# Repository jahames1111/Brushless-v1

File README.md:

# Brushless-v1
This will hopefully be my first real working drone. Previously, I have built things using brushed 8520 motors, but I could never get the drone to be light enough for those to work. This time, I will have a bigger budget and will be able to use brushless motors. 

3D: In github, also
https://cad.onshape.com/documents/dc8006e672f3f91329fdcc5b 
 
https://cad.onshape.com/documents/e8c6850fa68e1cd546790438 
 
https://cad.onshape.com/documents/d17096ea64e2407efe53b08a 

# BOM (so far)
|Part                                                            |Type      |Quantity|Unit price (USD)|Line total (USD)|Link                                                                                       |Vendor               |Funding    |Notes                                                  |
|----------------------------------------------------------------|----------|--------|----------------|----------------|-------------------------------------------------------------------------------------------|---------------------|-----------|-------------------------------------------------------|
|1203 6500KV 2-4S Brushless Motors (4PCS)                        |Part      |1       |39.99           |39.99           |https://www.amazon.com/SPARKHOBBY-Brushless-FPVRacer-Freestyle-Cinewhoop/dp/B0FF349Z37     |Amazon               |Grant      |4-pack 1.5mm shaft motors                              |
|CORVON 30A 4-in-1 Brushless ESC (6V-18V, 20x20mm)               |Part      |1       |26.99           |26.99           |https://www.amazon.com/CORVON-Brushless-Supports-Oneshot-Lightweight/dp/B0GTTVMRMG         |Amazon               |Grant      |2S-4S PWM/DShot 4-in-1 ESC                             |
|OVONIC 7.6V 100C 450mAh 2S LiPo Battery with XT30 (2-Pack)      |Part      |1       |20.37           |20.37           |https://www.amazon.com/OVONIC-Battery-Package-Including-Batteries/dp/B0D3F5SQ5T            |Amazon               |Grant      |Standard non-Prime price ($13.44 with Prime)           |
|JLC3DP PA12-HP Nylon 3D-Printed Drone Frame (frame (2).step)    |Part      |2       |8.28            |16.56           |https://jlc3dp.com/                                                                        |JLC3DP               |Grant      |MJF PA12-HP Nylon, Black, 2pcs                         |
|AOICRIE GY-521 MPU-6050 6-DOF Gyro/Accelerometer Module (3-Pack)|Part      |1       |14.99           |14.99           |https://www.amazon.com/AOICRIE-GY-521-Accelerometer-Gyroscope-Pre-Soldered/dp/B0D2TJVMNY   |Amazon               |Grant      |Pre-soldered headers, I2C IMU                          |
|Gemfan 3016 3-Blade 3-Inch Propellers 1.5mm Hole (16pcs)        |Part      |1       |12.98           |12.98           |https://www.amazon.com/Propeller-1108-1308-Brushless-Toothpick-Quadcopters/dp/B0DZPBVDD8   |Amazon               |Grant      |8 CW + 8 CCW props                                     |
|2.4GHz ELRS T-Receiver Antenna 100mm IPEX1 (3PCS)               |Part      |1       |9.99            |9.99            |https://www.amazon.com/2-4GHz-Antenna-90MM-ELRS-Compatible/dp/B0G7F842V8                   |Amazon               |Grant      |For ESP-NOW LR external antenna                        |
|ZHOFONET XT30 Male/Female Pigtail 16AWG Silicone Wire (5 Pairs) |Part      |1       |8.99            |8.99            |https://www.amazon.com/ZHOFONET-Pigtail-Female-Connector-Silicone/dp/B09F3CLKBG            |Amazon               |Grant      |Main battery connector lead                            |
|Mini MP1584EN 5V 3A DC-DC Buck Converter Module (6-Pack)        |Part      |1       |7.98            |7.98            |https://www.amazon.com/Converter-Voltage-Regulator-MP1584EN-Adjustable/dp/B0GHRPDKHW       |Amazon               |Grant      |Steps 2S battery down to 5.0V                          |
|HiLetgo BMP280-3.3 Atmospheric Pressure Barometer Sensor (5pcs) |Part      |1       |7.39            |7.39            |https://www.amazon.com/HiLetgo-Precision-BMP280-3-3-Atmospheric-Pressure/dp/B07VNDZ6N4     |Amazon               |Grant      |3.3V I2C barometer                                     |
|JLCPCB Custom Carrier PCB (brushless_Y16, 5pcs)                 |Part      |1       |4.00            |4.00            |https://jlcpcb.com/                                                                        |JLCPCB               |Grant      |Green 1.6mm OSP carrier PCB (5-pack)                   |
|JLCPCB & JLC3DP Shipping                                        |Shipping  |1       |11.70           |11.70           |https://jlcpcb.com/                                                                        |JLCPCB / JLC3DP      |Grant      |Combined shipping for carrier PCB and 3D-printed frames|
|Amazon Shipping (1203 Motors)                                   |Shipping  |1       |1.50            |1.50            |https://www.amazon.com/SPARKHOBBY-Brushless-FPVRacer-Freestyle-Cinewhoop/dp/B0FF349Z37     |Amazon               |Grant      |Shipping fee for motor set                             |
|SH 8p connector kit                                             |Part      |1       |19.99           |0.00            |https://www.amazon.com/Pre-Crimped-Connectors-Compatible-controller-SpeedyBee/dp/B0D2MQ85LK|Amazon               |Already own|Already own ($19.99 value for reproducibility)         |
|Seeed Studio XIAO ESP32S3 Sense Microcontroller                 |Part      |1       |13.99           |0.00            |https://www.amazon.com/Seeed-Studio-XIAO-ESP32S3-Microcontroller/dp/B0C69FFVHH             |Seeed Studio / Amazon|Already own|Already own ($13.99 value for reproducibility)         |
|GY-NEO6MV2 NEO-6M GPS Module with Ceramic Antenna               |Part      |1       |8.99            |0.00            |https://www.amazon.com/GY-NEO6MV2-NEO-6M-Module-Ceramic-Antenna/dp/B01D1D0F5M              |Amazon               |Already own|Already own ($8.99 value for reproducibility)          |
|Tax                                                             |Tax or fee|1       |8.56            |8.56            |                                                                                           |                     |Grant      |VA 5.03% Tax on $170.23 parts subtotal                 |
|Total                                                           |          |        |                |191.99          |                                                                                           |                     |           |                                                       |

# Wiring/Connections on PCB

| Net Name | Function / Signal | All Connected Pins |
| :--- | :--- | :--- |
| `2s` | Battery Voltage (`VBAT`) | `J5` Pin 1, `J7` Pin 7, `J8` Pin 2 |
| `5` | Regulated `+5V` Rail | `J1` Pin 1, `J6` Pin 1 |
| `3` | Regulated `+3.3V` Rail | `J1` Pin 3, `J3` Pin 1, `J4` Pin 1, `J9` Pin 1 |
| `g` | Common Ground (`GND`) | `J1` Pin 2, `J3` Pin 2, `J4` Pin 2, `J5` Pin 4, `J6` Pin 4, `J7` Pin 8, `J8` Pin 3, `J9` Pin 4 |
| `1` | ESC Motor 1 (`D0`) | `J2` Pin 1, `J7` Pin 6 |
| `2` | ESC Motor 2 (`D1`) | `J2` Pin 2, `J7` Pin 5 |
| `3` | ESC Motor 3 (`D2`) | `J2` Pin 3, `J7` Pin 4 |
| `4` | ESC Motor 4 (`D3`) | `J2` Pin 4, `J7` Pin 3 |
| `sda` | Shared I2C Data | `J2` Pin 5, `J3` Pin 4, `J4` Pin 4 |
| `scl` | Shared I2C Clock | `J2` Pin 6, `J3` Pin 3, `J4` Pin 3 |
| `rx` | UART (`D6` ➔ GPS `RX`) | `J2` Pin 7, `J9` Pin 2 |
| `tx` | UART (`D7` ➔ GPS `TX`) | `J1` Pin 7, `J9` Pin 3 |
| `vadc` | Battery Voltage Sense | `J1` Pin 6, `J8` Pin 1 |
| *No-Connect* | Unused Pins | `J1` Pin 4, `J1` Pin 5, `J5` Pin 2, `J5` Pin 3, `J6` Pin 2, `J6` Pin 3, `J7` Pin 1, `J7` Pin 2 |

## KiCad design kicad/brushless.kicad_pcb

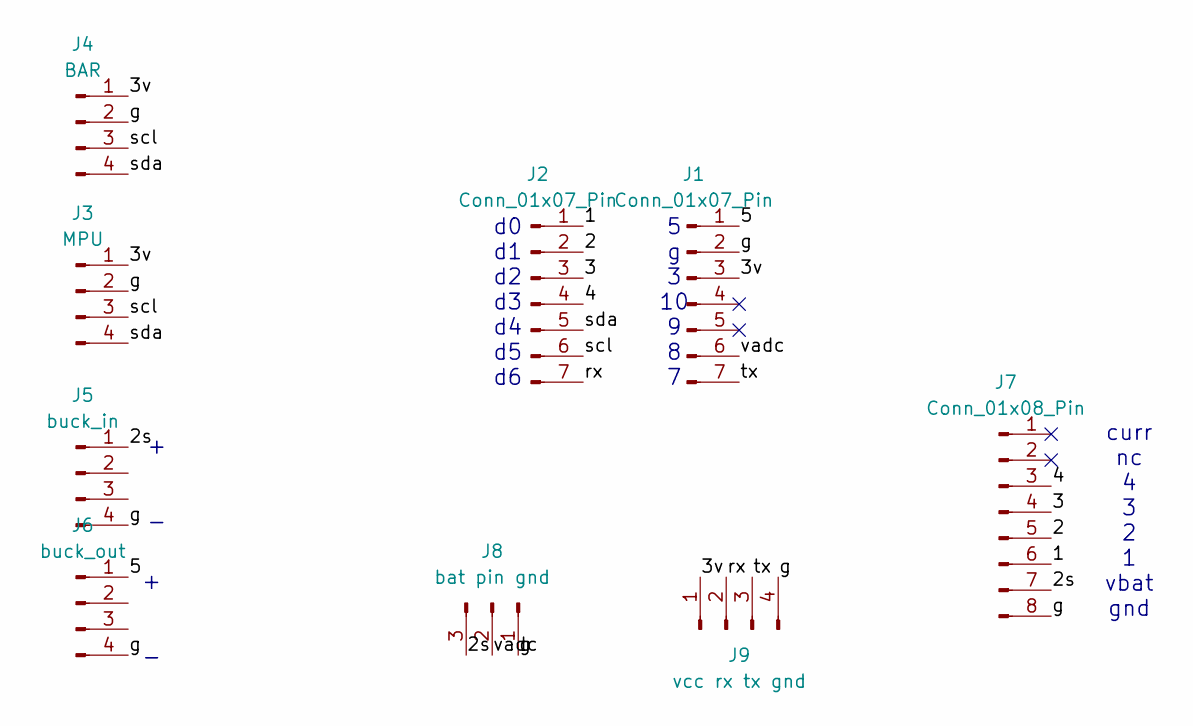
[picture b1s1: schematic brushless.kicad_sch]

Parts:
J1, J2: Conn_01x07_Pin; PinHeader_1x07_P2.54mm_Vertical
J3: MPU; PinHeader_1x04_P2.54mm_Vertical
J4: BAR; PinHeader_1x04_P2.54mm_Vertical
J5: buck_in; PinHeader_1x04_P2.54mm_Vertical
J6: buck_out; PinHeader_1x04_P2.54mm_Vertical
J7: Conn_01x08_Pin; PinHeader_1x08_P2.54mm_Vertical
J8: bat pin gnd; PinHeader_1x03_P2.54mm_Vertical
J9: vcc rx tx gnd; PinHeader_1x04_P2.54mm_Vertical

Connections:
/1: J2.1, J7.6
/2: J2.2, J7.5
/2s: J5.1, J7.7, J8.3
/3: J2.3, J7.4
/3v: J1.3, J3.1, J4.1, J9.1
/4: J2.4, J7.3
/5: J1.1, J6.1
/g: J1.2, J3.2, J4.2, J5.4, J6.4, J7.8, J8.1, J9.4
/rx: J2.7, J9.2
/scl: J2.6, J3.3, J4.3
/sda: J2.5, J3.4, J4.4
/tx: J1.7, J9.3
/vadc: J1.6, J8.2

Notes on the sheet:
+ -
5 g 3 10 9 8 7
curr nc 4 3 2 1 vbat gnd
d0 d1 d2 d3 d4 d5 d6

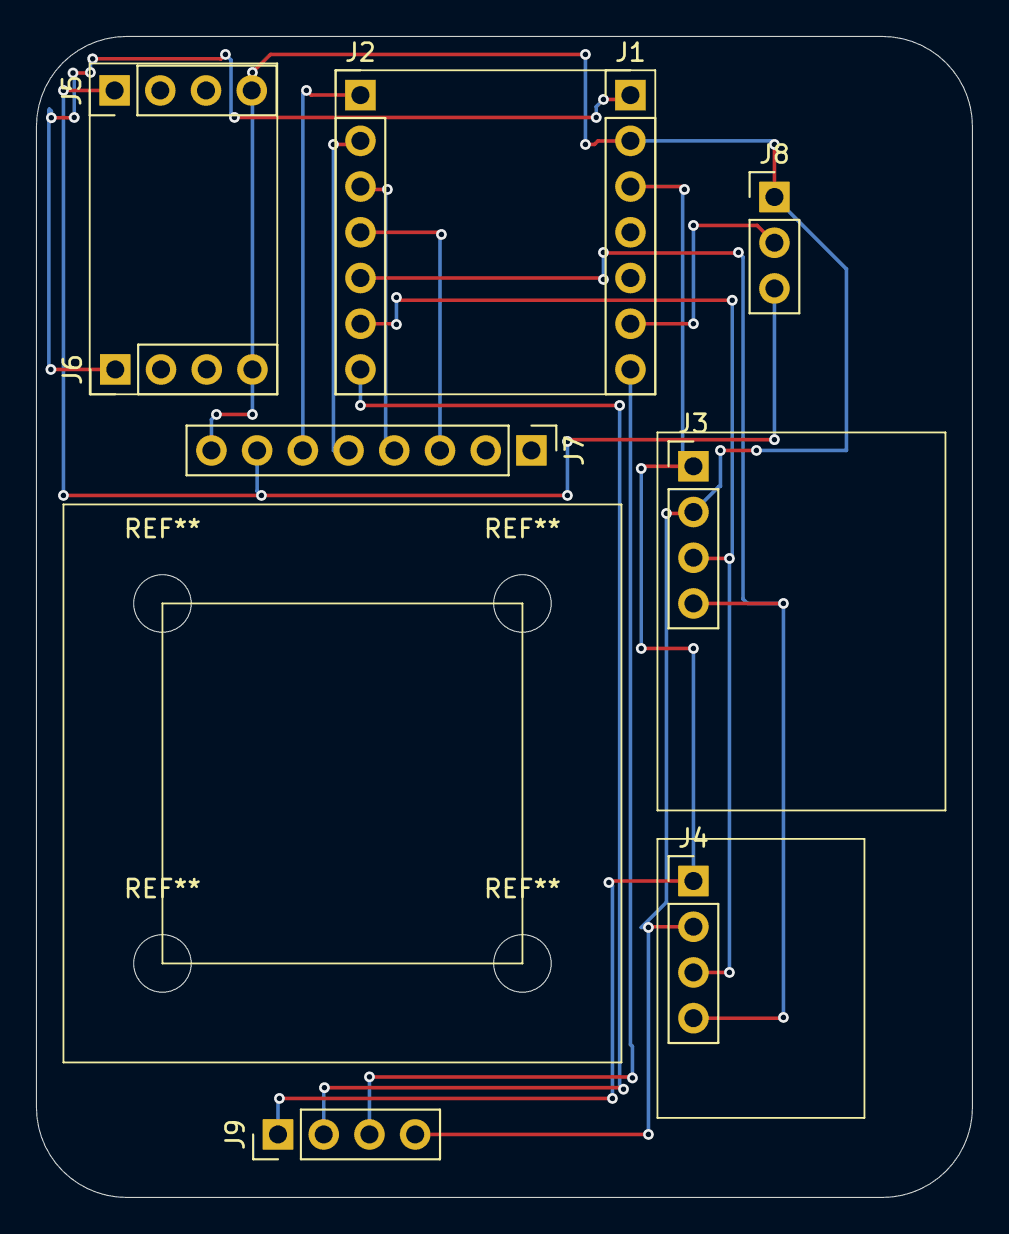
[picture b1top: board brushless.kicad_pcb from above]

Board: 2 copper layers, 52.0 x 64.5 mm, 9 parts (0 on the bottom side), 13 nets.
